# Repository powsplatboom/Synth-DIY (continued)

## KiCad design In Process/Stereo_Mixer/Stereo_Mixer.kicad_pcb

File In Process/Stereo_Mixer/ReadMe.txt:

Working in all ways except that pots are wired in reverse(left and right are reversed on output)
Will not be fixing, as this has been replaced by a control voltage modulated version also in progress.

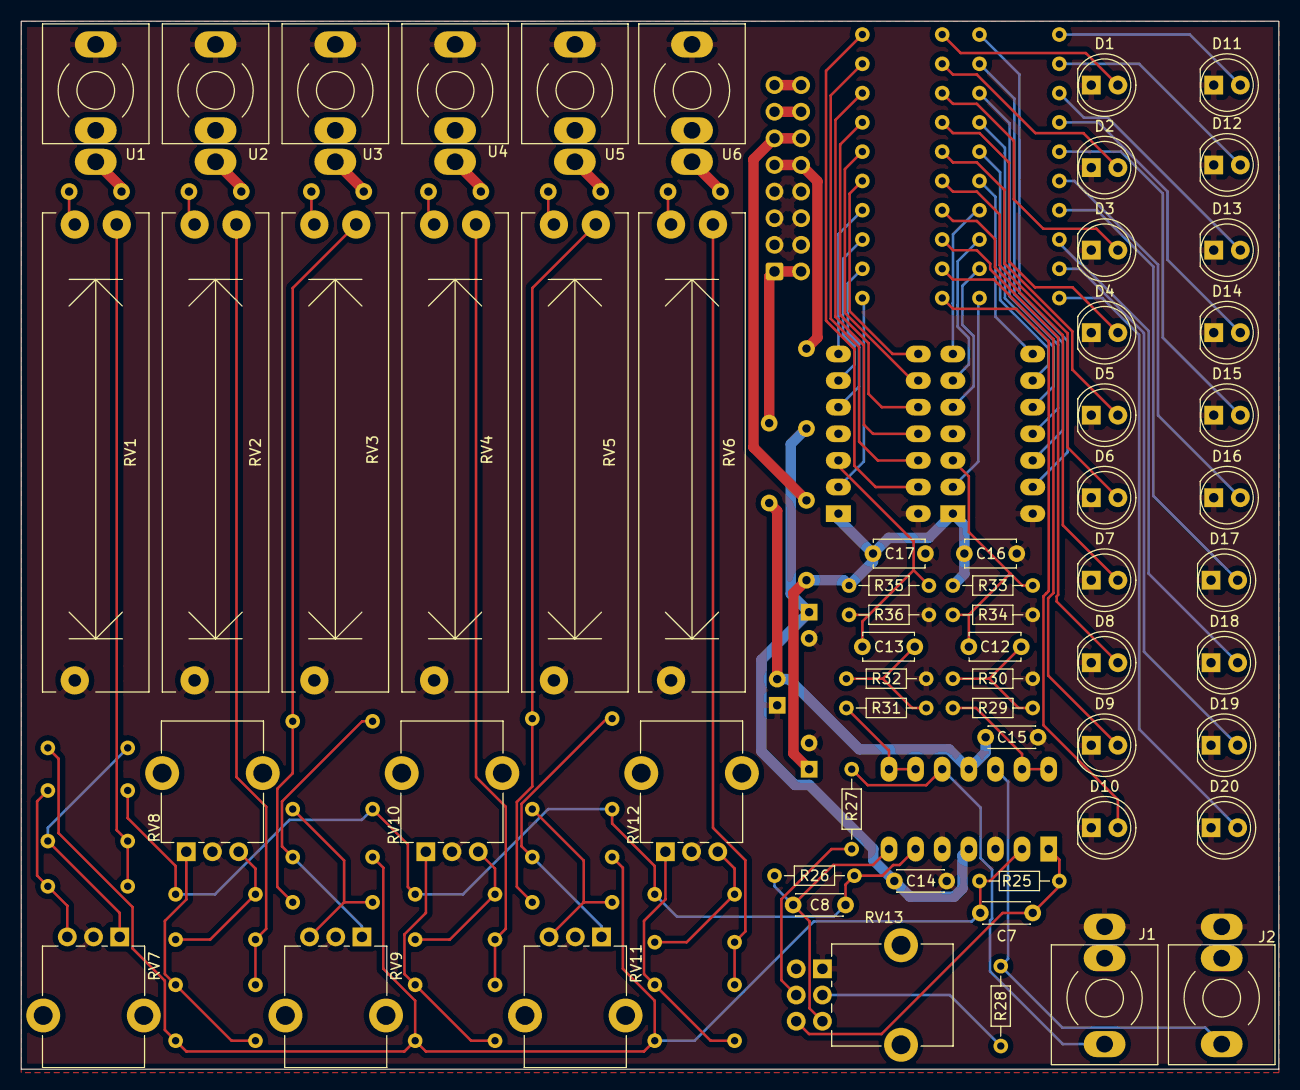
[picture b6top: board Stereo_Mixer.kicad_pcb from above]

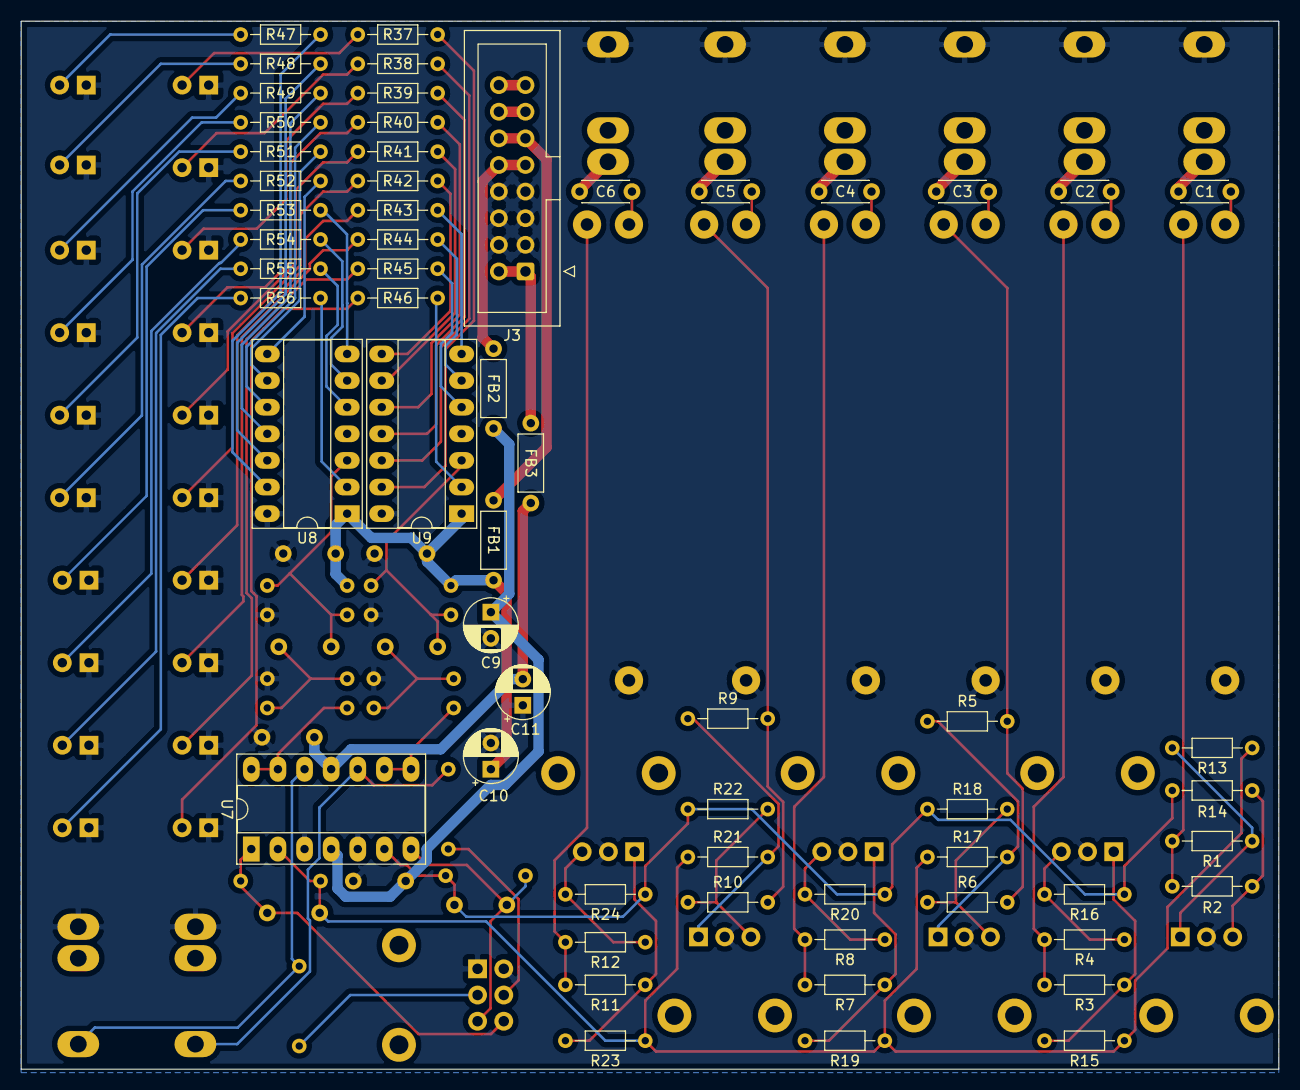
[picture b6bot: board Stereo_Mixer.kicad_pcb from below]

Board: 2 copper layers, 120.0 x 100.0 mm, 121 parts (60 on the bottom side), 93 nets.

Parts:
C1, C2, C3, C4, C5, C6: .1uf; C_Disc_D4.3mm_W1.9mm_P5.00mm
C7, C8: 22pf; C_Disc_D4.3mm_W1.9mm_P5.00mm
C9, C10, C11: 10uf; CP_Radial_D5.0mm_P2.50mm
C12, C13: 100nf; C_Disc_D4.7mm_W2.5mm_P5.00mm
C14, C15: 100nf; C_Disc_D4.3mm_W1.9mm_P5.00mm
C16, C17: 100n; C_Disc_D4.7mm_W2.5mm_P5.00mm
D1, D11: LED_RED; LED_D5.0mm
D2, D12: LED_YELLOW; LED_D5.0mm
D3, D4, D5, D6, D7, D8, D9, D10, D13, D14, D15, D16, D17, D18, D19, D20: LED; LED_D5.0mm
FB1, FB2, FB3: Ferrite_Bead_Small; L_Axial_L5.3mm_D2.2mm_P7.62mm_Horizontal_Vishay_IM-1
J1, J2: benjolin_1.6-eagle-import_PJ301_THONKICONN6; PJ-3001_Mono_Phone
J3: Conn_02x08_Odd_Even; IDC-Header_2x08_P2.54mm_Vertical
R1, R2, R3, R4, R5, R6, R7, R8, R9, R10, R11, R12, R13, R14, R15, R16, R17, R18, R19, R20, R21, R22, R23, R24: 20k; R_Axial_DIN0204_L3.6mm_D1.6mm_P7.62mm_Horizontal
R25, R26: 39K; R_Axial_DIN0204_L3.6mm_D1.6mm_P7.62mm_Horizontal
R27, R28: 1k; R_Axial_DIN0204_L3.6mm_D1.6mm_P7.62mm_Horizontal
R29, R30, R31, R32: 10k; R_Axial_DIN0204_L3.6mm_D1.6mm_P7.62mm_Horizontal
R33, R34, R35, R36: 100k; R_Axial_DIN0204_L3.6mm_D1.6mm_P7.62mm_Horizontal
R37, R38, R39, R40, R41, R42, R43, R44, R45, R46, R47, R48, R49, R50, R51, R52, R53, R54, R55, R56: 1K; R_Axial_DIN0204_L3.6mm_D1.6mm_P7.62mm_Horizontal
RV1, RV2, RV3, RV4, RV5, RV6: 100k; Potentiometer_slide_30mm
RV7, RV8, RV9, RV10, RV11, RV12: 50k; Potentiometer_Alpha_RD901F-40-00D_Single_Vertical_CircularH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
RV13: R_POT_Dual_Separate; Potentiometer_Alpha_RD902F-40-00D_Dual_Vertical_CircularHol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
U1, U2, U3, U4, U5, U6: PJ-3001f; PJ-3001_Mono_Phone
U7: TL074; DIP-14_W7.62mm_Socket_LongPads
U8: AudioMeter_right; DIP-14_W7.62mm_Socket_LongPads
U9: AudioMeter_left; DIP-14_W7.62mm_Socket_LongPads

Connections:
+5V: C10.1, C16.1, C17.1, FB1.1, R33.1, R35.1, U8.1, U9.1
GND: C9.2, C10.2, C11.1, C14.2, C15.1, C16.2, C17.2, D1.1, D2.1, D3.1, D4.1, D5.1, D6.1, D7.1, D8.1, D9.1, D10.1, D11.1, D12.1, D13.1, D14.1, D15.1, D16.1, D17.1, D18.1, D19.1, D20.1, J1.1, J2.1, J3.3, J3.4, J3.5, J3.6, J3.7, J3.8, R30.2, R32.2, R34.2, R36.2, RV1.3, RV2.3, RV3.3, RV4.3, RV5.3, RV6.3, RV7.2, RV8.2, RV9.2, RV10.2, RV11.2, RV12.2, RV13.1, RV13.4, U1.3, U2.3, U3.3, U4.3, U5.3, U6.3, U7.3, U7.5, U8.14, U9.14
LED1_1: R46.2, U9.2
LED1_2: R56.2, U8.2
LED2_1: R45.2, U9.5
LED2_2: R55.2, U8.5
LED3_1: R44.2, U9.6
LED3_2: R54.2, U8.6
LED4_1: R43.2, U9.7
LED4_2: R53.2, U8.7
LED5_1: R42.2, U9.8
LED5_2: R52.2, U8.8
LED6_1: R41.2, U9.9
LED6_2: R51.2, U8.9
LED7_1: R40.2, U9.10
LED7_2: R50.2, U8.10
LED8_1: R39.2, U9.11
LED8_2: R49.2, U8.11
LED9_1: R38.2, U9.12
LED9_2: R48.2, U8.12
LED10_1: R37.2, U9.13
LED10_2: R47.2, U8.13
Left: J1.3, R27.1, U7.10
unnamed: C1.1, RV1.1
unnamed: C1.2, U1.1
unnamed: C2.1, RV2.1
unnamed: C2.2, U2.1
unnamed: C3.1, RV3.1
unnamed: C3.2, U3.1
unnamed: C4.1, RV4.1
unnamed: C4.2, U4.1
unnamed: C5.1, RV5.1
unnamed: C5.2, U5.1
unnamed: C6.1, RV6.1
unnamed: C6.2, U6.1
unnamed: C7.1, R25.1, RV13.6, U7.1
unnamed: C7.2, R13.1, R15.1, R17.1, R19.1, R21.1, R23.1, R25.2, U7.2
unnamed: C8.1, R26.1, RV13.3, U7.7
unnamed: C8.2, R14.1, R16.1, R18.1, R20.1, R22.1, R24.1, R26.2, U7.6
unnamed: C11.2, C15.2, FB3.1, U7.11
unnamed: C12.1, R33.2, R34.1, U8.3
unnamed: C12.2, R29.2, R30.1
unnamed: C13.1, R35.2, R36.1, U9.3
unnamed: C13.2, R31.2, R32.1
unnamed: C9.1, C14.1, FB2.1, U7.4
unnamed: D1.2, R37.1
unnamed: D2.2, R38.1
unnamed: D3.2, R39.1
unnamed: D4.2, R40.1
unnamed: D5.2, R41.1
unnamed: D6.2, R42.1
unnamed: D7.2, R43.1
unnamed: D8.2, R44.1
unnamed: D9.2, R45.1
unnamed: D10.2, R46.1
unnamed: D11.2, R47.1
unnamed: D12.2, R48.1
unnamed: D13.2, R49.1
unnamed: D14.2, R50.1
unnamed: D15.2, R51.1
unnamed: D16.2, R52.1
unnamed: D17.2, R53.1
unnamed: D18.2, R54.1
unnamed: D19.2, R55.1
unnamed: D20.2, R56.1
unnamed: FB1.2, J3.11, J3.12
unnamed: FB2.2, J3.9, J3.10
unnamed: FB3.2, J3.1, J3.2
unnamed: J3.13, J3.14
unnamed: J3.15, J3.16
unnamed: R1.1, R13.2, RV7.1
unnamed: R1.2, R2.2, RV1.2
unnamed: R3.2, R4.2, RV2.2
unnamed: R5.2, R6.2, RV3.2
unnamed: R7.2, R8.2, RV4.2
unnamed: R10.1, R22.2, RV11.3
unnamed: R9.2, R10.2, RV5.2
unnamed: R11.1, R23.2, RV12.1
unnamed: R11.2, R12.2, RV6.2
unnamed: R12.1, R24.2, RV12.3
unnamed: R2.1, R14.2, RV7.3
unnamed: R3.1, R15.2, RV8.1
unnamed: R4.1, R16.2, RV8.3
unnamed: R5.1, R17.2, RV9.1
unnamed: R6.1, R18.2, RV9.3
unnamed: R7.1, R19.2, RV10.1
unnamed: R8.1, R20.2, RV10.3
unnamed: R9.1, R21.2, RV11.1
unnamed: R27.2, RV13.5
unnamed: R28.2, RV13.2
unnamed: R29.1, U7.13, U7.14
unnamed: R31.1, U7.8, U7.9
Right: J2.3, R28.1, U7.12

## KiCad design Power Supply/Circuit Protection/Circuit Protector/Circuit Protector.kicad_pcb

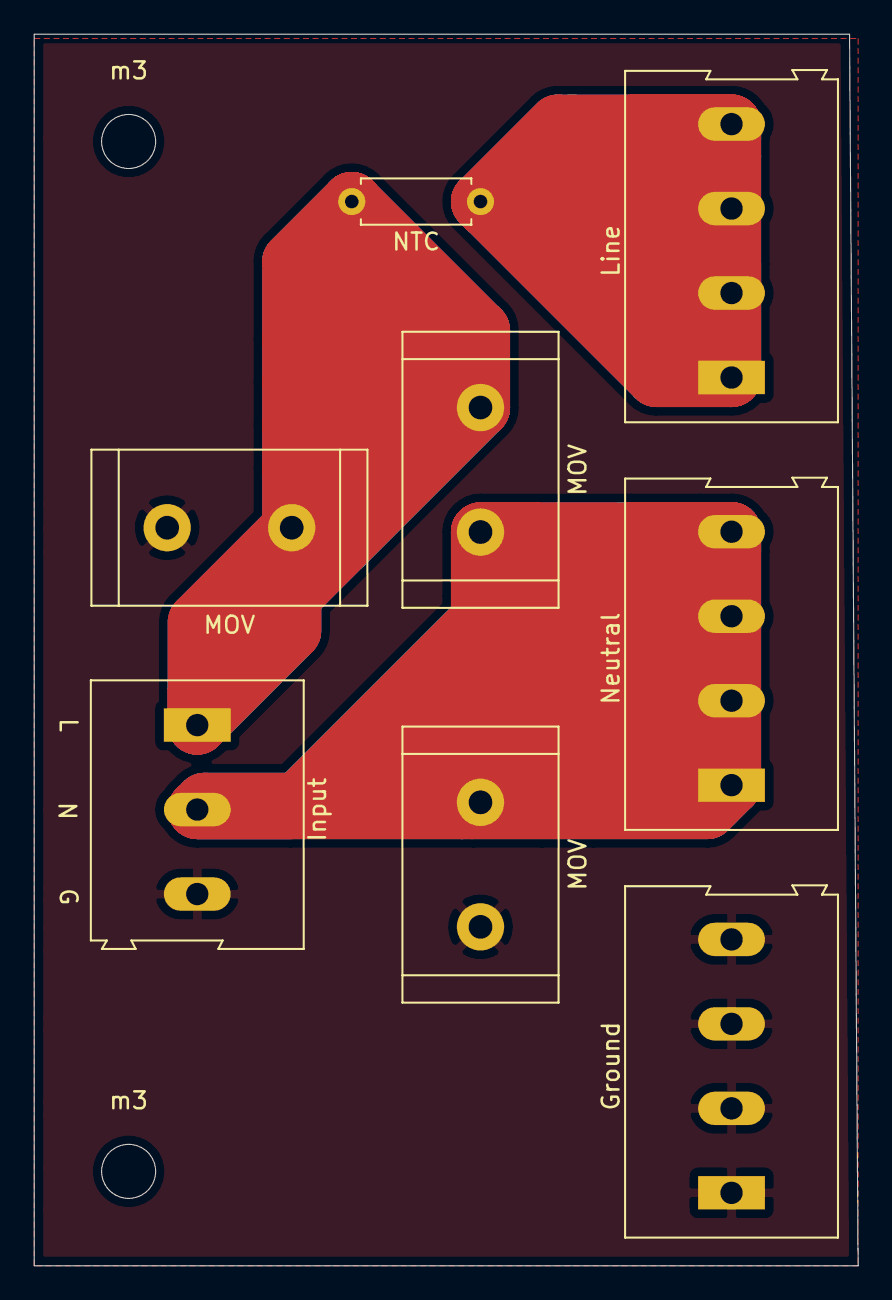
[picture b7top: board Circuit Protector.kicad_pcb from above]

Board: 2 copper layers, 48.8 x 72.9 mm, 10 parts (0 on the bottom side), 4 nets.

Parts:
Ground: Conn_01x04_Male; TerminalBlock_Altech_AK300-4_P5.00mm
Input: Conn_01x03_Male; TerminalBlock_Altech_AK300-3_P5.00mm
Line: Conn_01x04_Male; TerminalBlock_Altech_AK300-4_P5.00mm
MOV: Varistor; R_Radial_Power_L16.1mm_W9.0mm_P7.37mm
MOV#2, MOV#3: Varistor; R_Radial_Power_L16.1mm_W9.0mm_P7.37mm
NTC: Thermistor_NTC; R_Axial_DIN0207_L6.3mm_D2.5mm_P7.62mm_Horizontal
Neutral: Conn_01x04_Male; TerminalBlock_Altech_AK300-4_P5.00mm
m3, m3#2: MountingHole_3.2mm_M3

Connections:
unnamed: Ground.1, Ground.2, Ground.3, Ground.4, Input.3, MOV#2.2, MOV#3.2
unnamed: Input.1, MOV.1, MOV#3.1, NTC.2
unnamed: Input.2, MOV.2, MOV#2.1, Neutral.1, Neutral.2, Neutral.3, Neutral.4
unnamed: Line.1, Line.2, Line.3, Line.4, NTC.1
